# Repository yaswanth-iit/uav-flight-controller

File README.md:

## UAV Flight Controller
This repository consists of schematics, PCB layout, output files of UAV flight controller (Designed using kiCAD) [4-Layer]

[Schematics](https://raw.githubusercontent.com/yaswanth-iit/uav-flight-controller/master/quick%20view/schematics.pdf)

[PCB Layout](https://raw.githubusercontent.com/yaswanth-iit/uav-flight-controller/master/quick%20view/full%20pcb%20layout.pdf)

Used ICs:

* Microcontroller:  STM32F405RGT6, 25 MHz Clock
* EEPROM: 24CW1280T-I_OT
* FLASH Memory: W25N01GVZEIG_TR
* IMU: BMI088
* Magnetometer: IIS2MDCTR
* Barometer: BMP388
* PWM DRIVER: PCA9685BS
* SBUS INVERTER: 74LVC1G04GX4Z
* Voltage Regulator: LD39200PU33R
* USB TO UART: CH330
* ESD Suppressor: USBLC6-2SC6

# Top View

# Bottom view

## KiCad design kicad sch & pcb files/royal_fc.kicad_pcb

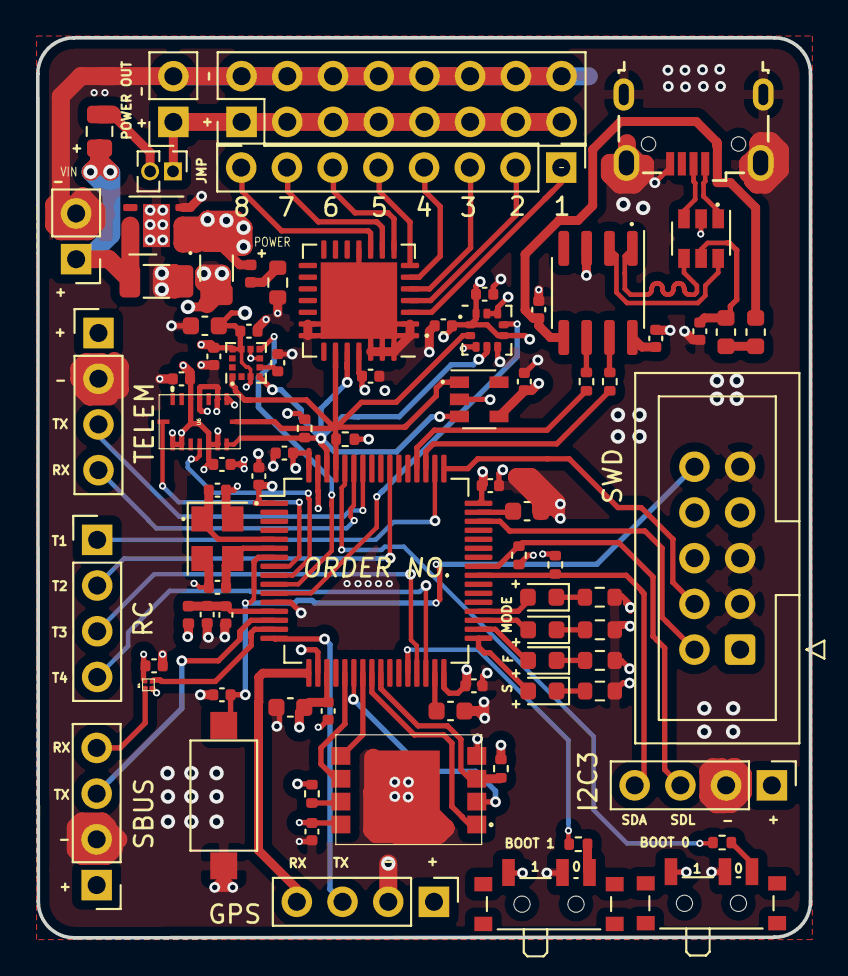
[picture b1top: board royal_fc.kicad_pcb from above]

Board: 4 copper layers, 42.9 x 50.0 mm, 81 parts (0 on the bottom side), 72 nets.

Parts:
8  7  6: Conn_01x08; PinHeader_1x08_P2.54mm_Vertical
C1, C3, C4, C5, C6, C8, C9, C14, C15, C16, C17, C18, C21, C22, C23, C24, C25, C26, C28, C29: 100nF; C_0402_1005Metric
C2: 4.7uF; C_0603_1608Metric
C7: 1uF; C_0402_1005Metric
C10, C11: 10uF; C_1206_3216Metric
C12, C13: 2.2uF; C_0603_1608Metric
C19, C20: 18pF; C_0402_1005Metric
C27: 10uF; C_0603_1608Metric
C30: 220nF; C_0402_1005Metric
D1: YE; Fuse_0402_1005Metric
D2: GR; LED_0603_1608Metric
D3: RE; LED_0603_1608Metric
D4, D5: BL; LED_0603_1608Metric
D6: D_Schottky; Fuse_0805_2012Metric
F1: Fuse_Small; Fuse_0603_1608Metric
FB1: Ferrite_Bead; L_0402_1005Metric
GPS: Conn_01x04; PinHeader_1x04_P2.54mm_Vertical
I2C3: Conn_01x04; PinHeader_1x04_P2.54mm_Vertical
IC1: LD39200PU33R; DFN-6-1EP_3x3mm_P1mm_EP1.5x2.4mm
IC2: 24CW1280T-I_OT; SOT-23-5
IC3: W25N01GVZEIG_TR
IC4: 74LVC1G04GX4Z; 74LVC1G04
IC5: IIS2MDCTR; LGA-12_2x2mm_P0.5mm
J1: Conn_01x02; PinSocket_1x02_P2.54mm_Vertical
J2: Ferrite_Bead; L_0603_1608Metric
J3: Conn_02x08_Odd_Even; PinHeader_2x08_P2.54mm_Vertical
JP1: Jumper; PinHeader_1x02_P1.27mm_Vertical
JP1#2: 1k; R_0603_1608Metric
R1: R1; R_0603_1608Metric
R2, R9, R11, R12: 10k; R_0402_1005Metric
R3, R4: 22; R_0402_1005Metric
R5: 2.2k; R_0603_1608Metric
R6, R8: 1k; R_0603_1608Metric
R13, R14, R15, R16: 2.2k; R_0402_1005Metric
RC: Conn_01x04; PinHeader_1x04_P2.54mm_Vertical
S1, S2: TDD01H0SB1R; SW_SPDT_PCM12
S3: SW_Push; SW_SPST_CK_RS282G05A3
SBUS: Conn_01x04; PinHeader_1x04_P2.54mm_Vertical
SWD1: Conn_02x05_Odd_Even; IDC-Header_2x05_P2.54mm_Vertical
TELEM: Conn_01x04; PinHeader_1x04_P2.54mm_Vertical
U1: USBLC6-2SC6; SOT-23-6
U2: CH330N; SOIC-8_3.9x4.9mm_P1.27mm
U3: STM32F405RGTx; LQFP-64_10x10mm_P0.5mm
U4: BMP388; ST_HLGA-10_2.5x2.5mm_P0.6mm_LayoutBorder3x2y
U5: PCA9685BS; QFN-28-1EP_6x6mm_P0.65mm_EP4.25x4.25mm
U6: BMI088; BMI008
USB1: USB_B_Micro; USB_Micro-B_Wuerth_629105150521
VIN1: Conn_01x02; PinHeader_1x02_P2.54mm_Vertical
Y1: 25MHz; Crystal_SMD_3225-4Pin_3.2x2.5mm

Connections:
+3V3: C1.1, C2.1, C3.1, C4.1, C5.1, C6.1, C10.1, C16.1, C17.1, C21.1, C22.1, C23.1, C24.1, C25.1, C26.1, C27.1, C28.1, C29.1, D1.2, FB1.2, GPS.1, I2C3.1, IC1.1, IC1.2, IC2.4, IC3.8, IC4.4, IC5.3, IC5.9, IC5.10, R11.2, R12.1, R13.2, R14.2, R15.2, R16.2, S1.1, S2.1, SBUS.1, SWD1.1, TELEM.1, U3.1, U3.19, U3.32, U3.48, U3.64, U4.1, U4.6, U4.10, U5.25, U6.3, U6.7, U6.10, U6.11, U6.14, U6.15
+5V: C14.1, F1.1, U2.5, USB1.1
/UART4_RX_INV: IC4.1, SBUS.4
BARO_INT: U3.11, U4.7
BOOT0: R2.1, U3.60
BOOT1: R9.1, U3.28
FLASH_CS!: IC3.1, U3.24
FLASH_MISO: IC3.2, U3.22
FLASH_MOSI: IC3.5, U3.23
FLASH_SCLK: IC3.6, U3.21
FLASH_WP!: IC3.3, R11.1, U3.25
GND: C1.2, C2.2, C3.2, C4.2, C5.2, C6.2, C7.2, C8.2, C9.2, C10.2, C11.2, C12.2, C13.2, C14.2, C15.2, C16.2, C17.2, C18.2, C19.2, C20.2, C21.2, C22.2, C23.2, C24.2, C25.2, C26.2, C27.2, C28.2, C29.2, C30.2, GPS.2, I2C3.2, IC1.3, IC1.7, IC2.2, IC3.4, IC3.9, IC4.2, IC5.6, IC5.8, J1.2, J3.2, J3.4, J3.6, J3.8, J3.10, J3.12, J3.14, J3.16, JP1#2.1, R1.1, R5.1, R6.1, R8.1, S1.2, S2.2, S3.2, SBUS.2, SWD1.3, SWD1.5, SWD1.9, TELEM.2, U1.2, U2.3, U3.12, U3.18, U3.63, U4.3, U4.5, U4.8, U4.9, U5.1, U5.2, U5.11, U5.20, U5.21, U5.26, U5.27, U5.28, U5.29, U6.4, U6.6, USB1.5, USB1.6, VIN1.2, Y1.2, Y1.4
I2C1_SCL: IC2.1, IC5.1, R16.1, U3.61, U4.2, U5.23, U6.8
I2C1_SDA: IC2.3, IC5.4, R15.1, U3.62, U4.4, U5.24, U6.9
I2C3_SCL: I2C3.3, R14.1, U3.41
I2C3_SDA: I2C3.4, R13.1, U3.40
INT_ACC: U3.8, U6.16
INT_GYR: U3.9, U6.12
LED_A: D2.2, U3.33
LED_B: D3.2, U3.34
LED_C: D4.2, U3.35
LED_D: D5.2, U3.36
MAGNET_INT: IC5.7, U3.10
NRST: C18.1, S3.1, SWD1.10, U3.7
unnamed: C9.1, J2.1, U1.5
unnamed: C12.1, U3.31
unnamed: C13.1, U3.47
unnamed: C15.1, U2.8
unnamed: C30.1, IC5.5
unnamed: D1.1, R1.2
unnamed: D2.1, R5.2
unnamed: D3.1, R6.2
unnamed: D4.1, JP1#2.2
unnamed: D5.1, R8.2
unnamed: D6.2, JP1.2
unnamed: F1.2, J2.2
unnamed: IC3.7, R12.2
unnamed: J1.1, J3.1, J3.3, J3.5, J3.7, J3.9, J3.11, J3.13, J3.15, JP1.1
unnamed: 8 7 6.1, U5.3
unnamed: 8 7 6.2, U5.4
unnamed: 8 7 6.3, U5.5
unnamed: 8 7 6.4, U5.6
unnamed: 8 7 6.5, U5.7
unnamed: 8 7 6.6, U5.8
unnamed: 8 7 6.7, U5.9
unnamed: 8 7 6.8, U5.10
unnamed: R2.2, S1.3
unnamed: R3.2, U2.6
unnamed: R4.2, U2.7
unnamed: R9.2, S2.3
OSC_IN: C19.1, U3.5, Y1.1
OSC_OUT: C20.1, U3.6, Y1.3
SWDCLK: SWD1.4, U3.49
SWDIO: SWD1.2, U3.46
TIM2_CH1: RC.1, U3.50
TIM2_CH2: RC.2, U3.55
TIM2_CH3: RC.3, U3.29
TIM2_CH4: RC.4, U3.30
UART4_RX: IC4.3, U3.15
UART4_TX: SBUS.3, U3.14
USART1_RX: TELEM.4, U3.59
USART1_TX: TELEM.3, U3.58
USART2_RX: GPS.4, U3.17
USART2_TX: GPS.3, U3.16
USART3_RX: R3.1, U3.52
USART3_TX: R4.1, U3.51
USB_D+: U1.3, USB1.3
USB_D-: U1.1, USB1.2
USB_OUT_D+: U1.4, U2.1
USB_OUT_D-: U1.6, U2.2
VCC: C11.1, D6.1, IC1.5, IC1.6, VIN1.1
VDDA: C7.1, C8.1, FB1.1, U3.13

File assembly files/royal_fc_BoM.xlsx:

| Item | Qty | Reference(s) | Value | Description | Component name : PCB footprint | Manufacturer | Part Number | Availability status | Distributor
 | 1 | 20 | C1, C3, C4, C5, C6, C8, C9, C14, C15, C16, C17, C18, C21, C22, C23, C24, C25, C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 | 100nF | 4.7uF+/-10% 10V X5R 1608 0603 | Capacitor_SMD:C_0402_1005Metric
 | 2 | 1 | C2, | 4.7uF | 1UF 16V 10% 0402 | Capacitor_SMD:C_0603_1608Metric
 | 3 | 1 | C7, | 1uF | 16V 0.1uF X5R 0402 10% | Capacitor_SMD:C_0402_1005Metric
 | 4 | 2 | C10, C11, | 10uF | 2.2uF+/-10% 16V X5R 1608 0603 | Capacitor_SMD:C_1206_3216Metric
 | 5 | 2 | C12, C13, | 2.2uF | 50V 18pF C0G 0402 5% | Capacitor_SMD:C_0603_1608Metric
 | 6 | 2 | C19, C20, | 18pF | 1206 MLCC X5R 10 uF +/- 5% 10 V | Capacitor_SMD:C_0402_1005Metric
 | 7 | 1 | C27, | 10uF | 0603 10uF+/-10% 10V X5R 1608 | Capacitor_SMD:C_0603_1608Metric
 | 8 | 1 | C30, | 220nF | 10V 0.22uF X5R 0402 10% | Capacitor_SMD:C_0402_1005Metric
 | 9 | 1 | D1, | Yellow | Light emitting diode | Fuse:Fuse_0402_1005Metric
 | 10 | 1 | D2, | Green | Light emitting diode | LED_SMD:LED_0603_1608Metric
 | 11 | 1 | D3, | Red | Light emitting diode | LED_SMD:LED_0603_1608Metric
 | 12 | 2 | D4, D5, | Blue | Light emitting diode | LED_SMD:LED_0603_1608Metric
 | 13 | 1 | D6, | Schottky diode | Schottky diode | D_Schottky:Diode_0805_2012Metric
 | 14 | 1 | F1, | 500mA | Fuse 500mA | Fuse:Fuse_0603_1608Metric
 | 15 | 1 | FB1, | 600 ohm @ 100Mhz | Ferrite bead | Ferrite_Bead_SMD:L_0402_1005Metric
 | 16 | 1 | FB2, | 600 ohm @ 100Mhz | Ferrite bead | Ferrite_Bead_SMD:L_0603_1608Metric
 | 17 | 1 | GPS1, | 01x04 | Generic connector, single row, 01x04 | PinHeader_1x04_P2.54mm_Vertical
 | 18 | 1 | I2C1, | 01x04 | Generic connector, single row, 01x04 | PinHeader_1x04_P2.54mm_Vertical
 | 19 | 1 | IC1, | LD39200PU33R | Voltage Regulator | DFN-6-1EP_3x3mm_P1mm_EP1.5x2.4mm
 | 20 | 1 | IC2, | 24CW1280T-I_OT | EEPROM | SOT-23-5
 | 21 | 1 | IC3, | W25N01GVZEIG_TR | FLASH memory | WSON 8x6-mm
 | 22 | 1 | IC4, | 74LVC1G04GX4Z | SBUS Inverter | SOT1269-2
 | 23 | 1 | IC5, | IIS2MDCTR | Magnetometer | LGA-12_2x2mm_P0.5mm
 | 24 | 1 | J1, | 01x02 | Generic connector, single row, 01x02 | PinSocket_1x02_P2.54mm_Vertical
 | 25 | 1 | J2, | 01x08 | Generic connector, single row, 01x08 | PinHeader_1x08_P2.54mm_Vertical
 | 26 | 1 | J3, | 02x08 | Generic connector, double row, 02x08 | PinHeader_2x08_P2.54mm_Vertical
 | 27 | 1 | JP1, | 01x02 | Jumper, normally open, small symbol | PinHeader_1x02_P1.27mm_Vertical
 | 28 | 4 | R2, R9, R11, R12, | 10k | Resistor | Resistor_SMD:R_0402_1005Metric
 | 29 | 2 | R3, R4, | 22 | Resistor | Resistor_SMD:R_0402_1005Metric
 | 30 | 2 | R1, R5, | 2.2k | Resistor | Resistor_SMD:R_0603_1608Metric
 | 31 | 3 | R6, R7, R8, | 1k | Resistor | Resistor_SMD:R_0603_1608Metric
 | 32 | 4 | R13, R14, R15, R16, | 2.2k | Resistor | Resistor_SMD:R_0402_1005Metric
 | 33 | 1 | RC1, | 01x04 | Generic connector, single row, 01x04 | PinHeader_1x04_P2.54mm_Vertical
 | 34 | 2 | S1, S2, | TDD01H0SB1R | SPDT switches | Button_Switch_SMD:SW_SPDT_PCM12
 | 35 | 1 | S3, | SPDT | Push button switch, generic, two pins | Button_Switch_SMD:SW_SPST_CK_RS282G05A3
 | 36 | 1 | SBUS1, | 01x04 | Generic connector, single row, 01x04 | PinHeader_1x04_P2.54mm_Vertical
 | 37 | 1 | SWD1, | 02x05 | Generic connector, double row, 02x05 | IDC-Header_2x05_P2.54mm_Vertical
 | 38 | 1 | TELEM1, | 01x04 | Generic connector, single row, 01x04 | PinHeader_1x04_P2.54mm_Vertical
 | 39 | 1 | U1, | USBLC6-2SC6 | Very low capacitance ESD protection diode, 2 data-line, SOT-23-6 | SOT-23-6
 | 40 | 1 | U2, | CH330N | USB serial converter, UART, SOIC-8 | SOIC-8_3.9x4.9mm_P1.27mm
 | 41 | 1 | U3, | STM32F405RGTx | ARM Cortex-M4 MCU, 1024KB flash, 128KB RAM, 168MHz, 1.8-3.6V, 51 GPIO, LQFP-64 | LQFP-64_10x10mm_P0.5mm
 | 42 | 1 | U4, | BMP388 | Barometer | Package_LGA:ST_HLGA-10_2.5x2.5mm_P0.6mm_LayoutBorder3x2y
 | 43 | 1 | U5, | PCA9685BS | 16-channel 12-bit PWM Fm+ I2C-bus LED controller RGBA QFN | QFN-28-1EP_6x6mm_P0.65mm_EP4.25x4.25mm
 | 44 | 1 | U6, | BMI088 | Accelerometer + Gyrometer | LGA 3.0mm x 4.5mm x 0.95mm
 | 45 | 1 | USB1, | USB_B_Micro | USB Micro Type B connector | Connector_USB:USB_Micro-B_Wuerth_629105150521_CircularHoles
 | 46 | 1 | VIN1, | 01x02 | Generic connector, single row, 01x02 | Connector_PinHeader_2.54mm:PinHeader_1x02_P2.54mm_Vertical
 | 47 | 1 | Y1, | 25MHz | Four pin crystal, GND on pins 2 and 4, small symbol | Crystal:Crystal_SMD_3225-4Pin_3.2x2.5mm

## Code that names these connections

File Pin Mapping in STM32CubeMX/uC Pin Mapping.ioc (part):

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Mcu.Name=STM32F405RGTx
Mcu.Package=LQFP64
Mcu.UserName=STM32F405RGTx
PA0-WKUP.Mode=Asynchronous
PA0-WKUP.Signal=UART4_TX
PA1.Mode=Asynchronous
PA1.Signal=UART4_RX
PA13.Mode=Serial_Wire
PA13.Signal=SYS_JTMS-SWDIO
PA14.Mode=Serial_Wire
PA14.Signal=SYS_JTCK-SWCLK
PA2.Mode=Asynchronous
PA2.Signal=USART2_TX
PA3.Mode=Asynchronous
PA3.Signal=USART2_RX
PA5.Mode=Full_Duplex_Master
PA5.Signal=SPI1_SCK
PA6.Mode=Full_Duplex_Master
PA6.Signal=SPI1_MISO
PA7.Mode=Full_Duplex_Master
PA7.Signal=SPI1_MOSI
PA8.Mode=I2C
PA8.Signal=I2C3_SCL
PB10.Signal=S_TIM2_CH3
PB11.Signal=S_TIM2_CH4
PB12.GPIOParameters=GPIO_Label
PB12.GPIO_Label=LED A
PB12.Signal=GPIO_Output
PB13.GPIOParameters=GPIO_Label
PB13.GPIO_Label=LED B
PB13.Signal=GPIO_Output
PB14.GPIOParameters=GPIO_Label
PB14.GPIO_Label=LED C
PB14.Signal=GPIO_Output
PB15.GPIOParameters=GPIO_Label
PB15.GPIO_Label=LED D
PB15.Signal=GPIO_Output
PB6.Mode=Asynchronous
PB6.Signal=USART1_TX
PB7.Mode=Asynchronous
PB7.Signal=USART1_RX
PB8.Mode=I2C
PB8.Signal=I2C1_SCL
PB9.Mode=I2C
PB9.Signal=I2C1_SDA
PC0.GPIOParameters=GPIO_Label
PC0.GPIO_Label=INT_ACC
PC0.Signal=GPXTI0
PC1.GPIOParameters=GPIO_Label
PC1.GPIO_Label=INT_GYR
PC1.Signal=GPXTI1
PC10.Mode=Asynchronous
PC10.Signal=USART3_TX
PC11.Mode=Asynchronous
PC11.Signal=USART3_RX
PC2.GPIOParameters=GPIO_Label
PC2.GPIO_Label=MAGNET_INT
PC2.Signal=GPXTI2
PC3.GPIOParameters=GPIO_Label
PC3.GPIO_Label=BARO_INT
PC3.Signal=GPXTI3
PC9.Mode=I2C
PC9.Signal=I2C3_SDA
PH0-OSC_IN.Mode=HSE-External-Oscillator
PH0-OSC_IN.Signal=RCC_OSC_IN
PH1-OSC_OUT.Mode=HSE-External-Oscillator
PH1-OSC_OUT.Signal=RCC_OSC_OUT
RCC.HSE_VALUE=25000000
RCC.SYSCLKFreq_VALUE=16000000
board=custom

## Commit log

2021-11-07 Created ReadMe
